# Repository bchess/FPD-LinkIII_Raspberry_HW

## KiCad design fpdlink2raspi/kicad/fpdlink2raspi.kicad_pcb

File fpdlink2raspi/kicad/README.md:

# fpdlink2raspi: KiCad PCB (rebuilt from the Gerbers)

The Altium source (`.PcbDoc`) was never published, so this KiCad 10 project was
**rebuilt** from the fabrication outputs in this repo:

| Input | What it gives |
|-------|---------------|
| `GerberX2/*` (Gerber X2, Altium 20.1) | copper, pads, vias, pours, mask, paste, drills, outline, mechanical layers |
| `Pick Place/*.txt` | reference, side, position and rotation of each part |
| `BOM/*.xlsx` | value, MPN, manufacturer, supplier, Altium LibRef |
| `fpdlink2raspi_SCH_0v4.PDF` | its bookmarks hold Altium's full netlist (net names and pin numbers) |

Open `fpdlink2raspi.kicad_pro` in KiCad 10. `render_top.png` is a KiCad 3D render.

## What you get

* A 4-layer board, 39 x 56 mm, with the stackup from the fab drawing (0.119 / 1.2 / 0.119 mm FR-4, 35 µm Cu, 1.6 mm total).
* 148 footprints: 136 placed parts, the 6 not-fitted parts, 4 mounting holes. Every pad is reconstructed
  exactly: shape, size, corner radius, mask and paste margins, and the segmented exposed-pad paste for U3/U4.
* 100 nets with the schematic's net names. Every pad carries its schematic pin number (U3 pins 1 to 49,
  J1 pins 1 to 15 plus S1/S2, and so on).
* Tracks and arcs, 171 vias (via-in-pad tenting as in Altium), 11 filled zones (inner planes and top pours),
  and the copper text labels ("PoC", "3V3", the zhaw/InES logo, ...).
* A project footprint library, `fpdlink2raspi.pretty`, with all 30 footprints (`fp-lib-table` is included).
* Courtyards (Altium M15/M16) and assembly drawings (M13/M14) inside each footprint. The other Altium
  mechanical layers are kept on named User layers (`User.1` to `User.8`).
* BOM data is in footprint fields. Not-fitted parts (C33, R4, R5, R6, R27, R29) are marked DNP, because the
  variant left them out of pick-and-place. Their identity comes from matching their copper against the netlist.

## How it was checked

* **Gerber round trip.** I exported Gerbers and drills from this KiCad board and compared them geometrically
  with the original Altium files.
  * All 4 copper layers, bottom solder mask and both paste layers match to better than 10 µm.
  * All 185 drill hits match in position and size.
  * The one remaining difference is on top solder mask. KiCad rounds the corners of rectangular pads' mask
    openings with a 50 µm radius; Altium leaves them sharp. That totals 0.16 mm² over the whole board.
* **Netlist.** The pin numbering was solved so that the copper connectivity agrees with the schematic netlist.
  * 21 pins carry a different name in the schematic. All of them are hierarchical-harness aliases of the same
    net: J1's CSI pins to U3's `D_*` nets, U1 GPIOs to U3 GPIOs, I2C through R33/R34, and `REF_CLK`/`TI_*`.
    Each copper net uses the user-given name.
  * There are no shorts between differently named nets and no nets split into islands.
* **KiCad DRC:** 0 clearance errors and 0 unconnected items.
  * There are 48 *courtyard overlap* errors. They are real overlaps in the original Altium layout (Altium
    doesn't check these by default).
  * There are 3 harmless "footprint differs from library" warnings.

## Things that are not in the Gerbers

* **Silkscreen.** The real board has a legend, but no overlay Gerber was published, so `F/B.SilkS` are
  empty. Reference designators are on the Fab layers.
* **Schematic.** There is no `.kicad_sch`. The nets and pin numbers are on the board, so a schematic drawn
  later can be linked with *Update PCB from Schematic*. Use the same references and pin numbers.
* **Altium design rules.** Only the basics are carried over: 0.125 mm clearance, 0.06 mm mask expansion
  (0.05 mm on fine-pitch pads), and 0.15 mm via drills. Altium also had a 1 mm pour-to-diff-pair clearance.
  It is visible in the existing fills, but it's not a KiCad rule.
* **Zones.** The zones are pre-filled with Altium's exact copper. Their outlines follow the filled shapes.
  If you *refill* in KiCad, it recomputes clearances with its own rules, so check the CSI diff pairs and the
  RF lines after a refill.
* **Footprint names.** They are descriptive (for example `VQFN-48-1EP_7x7mm_P0.5mm_EP4.1x4.1mm`). The
  footprints are the Altium ones reconstructed, not KiCad stock library parts, and have no 3D models.
* **BOM values** come from `BOM/*.xlsx`. That includes the 9 V PoC changes described in the top-level
  README, not the values printed in the schematic PDF.

## Regenerating

`conversion/` holds the converter. It runs in KiCad's bundled Python and needs `shapely`, `numpy` and
`pymupdf` installed into a `pylib` directory next to `conversion/`:

```bash
KP=../KiCad.app/Contents/Frameworks/Python.framework/Versions/Current/bin/python3
$KP -m pip install --target pylib "shapely==2.0.6" "numpy<2.1" pymupdf
$KP conversion/build_kicad.py .. out        # writes out/fpdlink2raspi.kicad_pcb etc.
```

`compare.py <fpdlink2raspi dir> <dir with KiCad-exported Gerbers> ''` repeats the Gerber round-trip check.

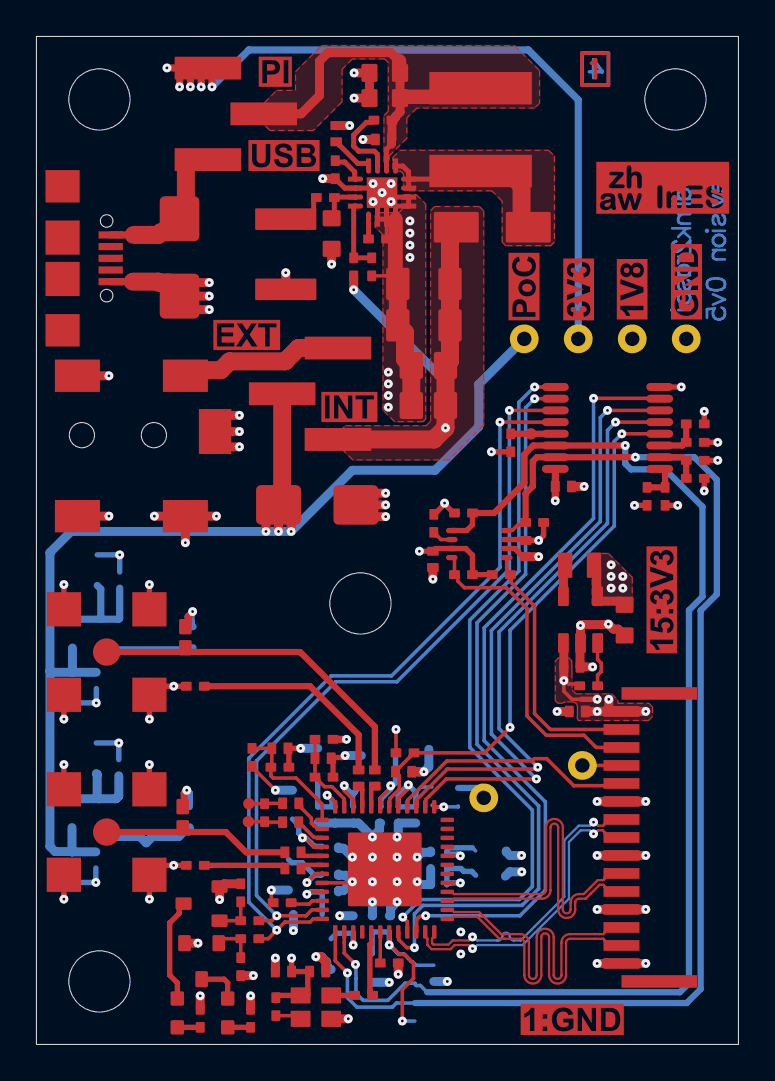
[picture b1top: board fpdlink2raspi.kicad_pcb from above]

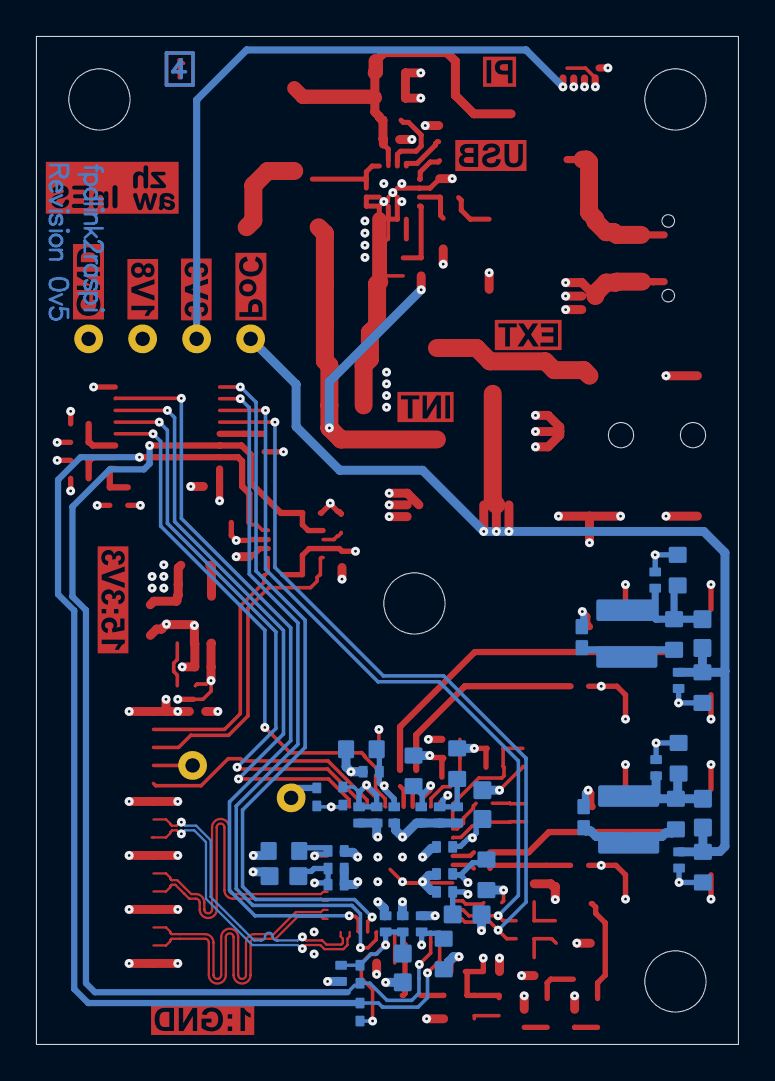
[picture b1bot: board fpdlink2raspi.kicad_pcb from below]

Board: 4 copper layers, 39.0 x 56.0 mm, 148 parts (47 on the bottom side), 84 nets.

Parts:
C1, C3, C4, C5, C6, C8, C10, C12, C14, C20, C24, C30, C37, C38, C42, C53: 100n; C_0402_1005Metric
C2, C21, C22, C25, C26, C28, C31, C32, C35, C40, C44, C46: 10n; C_0402_1005Metric
C7, C9, C11, C13, C23, C29, C51, C52: 10u; C_0603_1608Metric
C15, C17, C36, C41: 33n; C_0402_1005Metric
C16, C18: 15n; C_0402_1005Metric
C19, C27: 1u; C_0402_1005Metric
C33, C57: 4u7; C_0402_1005Metric
C34, C39, C43, C45: 4u7; C_0603_1608Metric
C47, C48: 22u; C_1206_3216Metric
C49, C50: 1u; C_0805_2012Metric
C54: 47n; C_0402_1005Metric
C55: 15n; C_0603_1608Metric
C56: 1u; C_1812_4532Metric
C58: 22u; C_0603_1608Metric
D1: Green, 3.2 V, 140°; LED_0603_1608Metric
D2: Yellow, 2 V, 140°; LED_0603_1608Metric
D3: SMBJ5.0A; D_SMB
D4: B340LA-13-F; D_SMA
D5: SMBJ24A; D_SMB
J1: SFW15R-1ST; Amphenol_SFW15R-1STE1LF_1x15_P1.00mm_Horizontal
J2: PJ-075DH-SMT-TR; CUI_PJ-075CH-SMT_DC_Jack
J3: Micro USB; Wurth_629105136821_USB_Micro-B
L1, L5: 10u; L_Murata_LQH3NP_3.0x3.0mm
L2, L6: 1k 0.4A 0.5R; L_0603_1608Metric
L3, L7: 330R 0.7A 280mR; L_0402_1005Metric
L4, L8: 47R 0.45A 450mR; L_0402_1005Metric
L9, L10, L11, L12: 120R 3A 25mR; L_0603_1608Metric
L13: 12uH, 2.6A; L_Wurth_WE-LQS-6045
L14: 2u2; L_Murata_DFE201612E
MH1, MH2, MH3, MH4: MountingHole; MountingHole_3.4mm_NPTH
Q1, Q2: BSS138-13-F; SOT-23
R1, R18, R19, R26, R35, R36, R37, R41, R43: 0R; R_0402_1005Metric
R2, R3, R29, R32, R42: 10k; R_0402_1005Metric
R4, R5, R6, R7, R8, R9, R14: 1k; R_0402_1005Metric
R10, R11, R25, R27: 4k7; R_0402_1005Metric
R12, R13, R33, R34: 47k; R_0402_1005Metric
R15: 1k2; R_0402_1005Metric
R16, R39: 390R; R_0402_1005Metric
R17, R22: 4k02; R_0603_1608Metric
R20, R21: 118k; R_0402_1005Metric
R23, R24: 49R9; R_0402_1005Metric
R28: 78k7; R_0402_1005Metric
R30: 100R; R_0402_1005Metric
R31: 97k6; R_0402_1005Metric
R38: 63k4; R_0402_1005Metric
R40: 60k4; R_0402_1005Metric
TP1: 0v1 27.04.20 gana Review release.; TestPoint_THTPad_D1.6mm_Drill0.8mm
TP2: PIC301; TestPoint_Pad_D0.635mm
TP3: A0; TestPoint_THTPad_D1.6mm_Drill0.8mm
TP4, TP5: TestPoint; TestPoint_Pad_D0.635mm
TP6, TP7, TP9: TestPoint; TestPoint_THTPad_D1.6mm_Drill0.8mm
TP8: 2 MHz (1.6 - 2.6 MHz); TestPoint_THTPad_D1.6mm_Drill0.8mm
U1: TCA9534APW; TSSOP-16_4.4x5mm_P0.65mm
U2: TCA9406DCUR; TI_US8_DCU_2.3x2.0mm_P0.5mm
U3: DS90UB954TRGZxQ1; VQFN-48-1EP_7x7mm_P0.5mm_EP4.1x4.1mm
U4: TPS55340RTE; WQFN-16-1EP_3x3mm_P0.5mm_EP1.7x1.7mm
U5: LM3671MFX-1.8/NOPB; SOT-23-5
X1, X2: SMA JACK STR; Molex_73251-1350_SMA_Vertical
X3, X4: 1241150-3; TE_1241150-3_1x03_P2.54mm_SMD
Y1: SG-210STF 25.0000M; Oscillator_Epson_SG-210STF_2.5x2.0mm

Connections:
1V8: C1.2, C2.2, C3.2, C6.2, C58.2, L9.1, L10.1, L11.1, L12.1, L14.2, R2.1, R3.2, R4.2, R5.2, R6.2, R10.2, R11.2, R14.1, R27.2, R28.2, R29.2, TP9.1, U1.16, U2.3, U5.4, Y1.4
3V3: C4.2, C5.2, C57.2, J1.15, R12.2, R13.2, R15.2, R16.2, R43.1, TP6.1, U2.7, U5.1, X3.3
D_CLK_0_N: J1.8, U3.11
D_CLK_0_P: J1.9, U3.12
D_DATA_0_N: J1.2, U3.13
D_DATA_0_P: J1.3, U3.14
D_DATA_1_N: J1.5, U3.15
D_DATA_1_P: J1.6, U3.16
GND: C1.1, C2.1, C3.1, C4.1, C5.1, C6.1, C7.1, C8.1, C9.1, C10.1, C11.1, C12.1, C13.1, C14.1, C19.1, C20.1, C21.1, C22.1, C23.1, C24.1, C25.1, C26.1, C27.1, C28.1, C29.1, C30.1, C31.1, C32.1, C33.1, C34.1, C35.1, C37.1, C38.1, C39.1, C40.1, C42.1, C43.1, C44.1, C45.1, C46.1, C47.2, C48.2, C49.2, C50.1, C51.1, C52.1, C53.1, C54.1, C55.1, C56.1, C57.1, C58.1, D3.2, D5.2, J1.1, J1.4, J1.7, J1.10, J2.2, J2.3, J2.4, J2.5, J3.5, Q1.2, Q2.2, R7.1, R8.1, R9.1, R20.1, R21.1, R23.1, R24.1, R31.1, R32.1, R35.1, R36.1, R40.1, R41.1, R42.1, TP8.1, U1.8, U2.2, U3.44, U3.49, U4.6, U4.10, U4.11, U4.12, U4.13, U4.14, U4.17, U5.2, X1.2, X1.3, X1.4, X1.5, X2.2, X2.3, X2.4, X2.5, Y1.2
IDX: C38.2, R29.1, R32.2, U3.35
MODE: C37.2, R28.1, R31.2, U3.37
NetC9_2: C9.2, C10.2, L1.1, L2.2, R17.1
NetC13_2: C13.2, C14.2, L5.1, L6.2, R22.1
NetC15_1: C15.1, U3.41
NetC15_2: C15.2, L4.2, X1.1
NetC16_1: C16.1, R23.2
NetC16_2: C16.2, U3.42
NetC17_1: C17.1, U3.32
NetC17_2: C17.2, L8.2, X2.1
NetC18_1: C18.1, R24.2
NetC18_2: C18.2, U3.33
NetC23_2: C23.2, C24.2, C25.2, C26.2, L10.2, U3.36, U3.45
NetC27_2: C27.2, C28.2, L11.2, U3.17
NetC29_2: C29.2, C30.2, C31.2, C32.2, L12.2, U3.31, U3.40
NetC33_2: C33.2, R27.1, U1.4, U3.30
NetC34_2: C34.2, C35.2, U3.3
NetC36_1: C36.1, R30.2, TP4.1
NetC36_2: C36.2, U3.38
NetC39_2: C39.2, C40.2, U3.20
NetC41_1: C41.1, R30.1, TP5.1
NetC41_2: C41.2, U3.39
NetC43_2: C43.2, C44.2, U3.43
NetC45_2: C45.2, C46.2, U3.34
NetC47_1: C47.1, C48.1, C49.1, C50.2, D4.1, R38.2, X4.3
NetC51_2: C51.2, C52.2, C53.2, L13.1, R37.1, U4.2, X3.2
NetC54_2: C54.2, U4.4
NetC55_2: C55.2, R39.1, U4.7
NetC56_2: C56.2, R39.2
NetD1_1: D1.1, Q1.3
NetD1_2: D1.2, R15.1
NetD2_1: D2.1, Q2.3
NetD2_2: D2.2, R16.1
NetD3_1: D3.1, J3.1, X3.1
NetD4_2: D4.2, L13.2, U4.1, U4.15, U4.16
NetJ1_11: J1.11, U3.28
NetJ1_12: J1.12, TP3.1
NetJ1_13: J1.13, R12.1, U2.8
NetJ1_14: J1.14, R13.1, U2.1
NetJ2_1: J2.1, X4.1
NetL1_2: L1.2, L3.1, R17.2
NetL3_2: L3.2, L4.1
NetL5_2: L5.2, L7.1, R22.2
NetL7_2: L7.2, L8.1
NetL14_1: L14.1, U5.5
NetQ1_1: Q1.1, R18.2, R20.2
NetQ2_1: Q2.1, R19.2, R21.2
NetR1_1: R1.1, Y1.3
NetR2_2: R2.2, Y1.1
NetR3_1: R3.1, TP2.1, U1.13
NetR4_1: R4.1, R7.2, U1.1
NetR5_1: R5.1, R8.2, U1.2
NetR6_1: R6.1, R9.2, U1.3
NetR10_1: R10.1, R33.1, U1.15, U2.4, U3.1
NetR11_1: R11.1, R34.1, U1.14, U2.5, U3.2
NetR14_2: R14.2, U2.6
NetR25_1: R25.1, R26.2, U3.25
NetR35_2: R35.2, U3.6
NetR36_2: R36.2, U3.46
NetR37_2: R37.2, U4.3
NetR38_1: R38.1, R42.2, U4.8
NetR40_2: R40.2, U4.9
NetR41_2: R41.2, U4.5
NetR43_2: R43.2, U5.3
NetTP1_1: R26.1, TP1.1
NetU1_5: U1.5, U3.27
NetU1_6: U1.6, U3.26
NetU1_7: U1.7, U3.10
NetU1_9: U1.9, U3.9
NetU3_8: U1.10, U3.8
REF_CLK: R1.2, U3.5
TI_LOCK: R19.1, U1.12, U3.48
TI_PASS: R18.1, U1.11, U3.47
VDDIO: C19.2, C20.2, C21.2, C22.2, C42.2, L9.2, R25.2, R33.2, R34.2, U3.7, U3.29
V_POC: C7.2, C8.2, C11.2, C12.2, D5.1, L2.1, L6.1, TP7.1, X4.2

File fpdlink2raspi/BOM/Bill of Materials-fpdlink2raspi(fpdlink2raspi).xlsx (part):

Name | Description | Designator | Quantity | LibRef | Supplier 1 | Supplier Part Number 1 | Manufacturer 1 | Manufacturer Part Number 1
100n | SMD 100 nF, 50V, X7R, 0402, 10% | C1, C3, C4, C5, C6, C8, C10, C12, C14, C20, C24, C30, C37, C38, C42, C53 | 16 | C0402_100N_X7R_50V_10PCT | Mouser | 81-GCM155R71H104KE2J | Murata | GCM155R71H104KE02J
10n | SMD 10 nF, 16V, X7R, 0402, 10% | C2 | 1 | C0402_010N_X7R_16V_10PCT | Mouser | 81-GRM36X103K16 | Murata | GRM155R71C103KA01D
10u | 10µF, 25V, +/-20%, X5R, 0603 | C7, C9, C11, C13, C23, C29, C51, C52 | 8 | C0603_010U_X5R_25V | Digi-Key | 490-7202-6-ND | Murata | GRM188R61E106MA73D
33n | SMD 33 nF, 50V, X7R, 0402, 10% | C15, C17, C36, C41 | 4 | C0402_033N_X7R_50V_10PCT | Digi-Key | 445-6896-1-ND | TDK | CGA2B3X7R1H333K050BB
15n | SMD 15 nF, 50V, X7R, 0402, 10% | C16, C18 | 2 | C0402_015N_X7R_50V_10PCT | Digi-Key | 445-6894-1-ND | TDK | CGA2B3X7R1H153K050BB
1u | SMD 1 µF, 35V, X5R, 0402, 10% | C19, C27 | 2 | C0402_001U_X5R_35V_10PCT | Digi-Key | 587-6008-1-ND | Taiyo Yuden | GMK105ABJ105KV-F
10n | SMD 10 nF, 50V, X7R, 0402, 10% | C21, C22, C25, C26, C28, C31, C32, C35, C40, C44, C46 | 11 | C0402_010N_X7R_50V_10PCT | Digi-Key | 490-4762-1-ND | Murata | GCM155R71H103KA55D
4u7 | 4.7µF, 25V, +/-10%, X5R, 0603 | C34, C39, C43, C45 | 4 | C0603_04U7_X5R_25V | Digi-Key | 490-7203-1-ND | Murata | GRM188R61E475KE11D
22u | 22µF ±20% 35V Ceramic Capacitor X5R 1206 (3216 Metric) | C47, C48 | 2 | C1206_022U_X5R_35V_20PCT | Digi-Key | 445-8045-1-ND | TDK | C3216X5R1V226M160AC
1u | 1µF ±10% 35V Ceramic Capacitor X7R 0805 (2012 Metric) | C49, C50 | 2 | C0805_001U_X7R_35V_10PCT | Digi-Key | 587-1438-1-ND | Taiyo Yuden | GMK212B7105KG-T
47n | 0.047µF ±10% 16V Ceramic Capacitor X7R 0402 (1005 Metric) | C54 | 1 | C0402_047N_X7R_16V_10PCT | Mouser | 81-GRM155R71C473KA01 | Murata | GRM155R71C473KA01D
15n | 15000pF ±5% 25V Ceramic Capacitor C0G, NP0 0603 (1608 Metric) | C55 | 1 | C0603_15N_C0G_25V_5PCT |  |  | KEMET | C0603C153J3GACTU
1u | 1µF ±10% 50V Ceramic Capacitor X7R 1812 (4532 Metric) | C56 | 1 | C1812_001U_X7R_50V_10PCT | LCSC | C452759 | KEMET | C1812C105K5RACTU
4u7 | SMD 4.7 µF, 10V, X5R, 0402, 20% | C57 | 1 | C0402_04U7_X5R_10V_20PCT | Mouser | 81-GRM155R61A475MEAD | Murata | GRM155R61A475MEAAD
22u | SMD 22 µF, 6.3V, X5R, 0603, 20% | C58 | 1 | C0603_022U_X5R_6V3_20PCT | Digi-Key | 490-13241-1-ND | Murata | GRM186R60J226ME15D
Green, 3.2 V, 140° | WL-SMCD SMD Mono-color Chip LED Diffused, size 0603, Green, 3.2 V, 140° | D1 | 1 | D_WE_150060GS55040 | Mouser | 710-150060GS55040 | Wurth Electronics | 150060GS55040
Yellow, 2 V, 140° | WL-SMCD SMD Mono-color Chip LED Diffused, size 0603, Yellow, 2 V, 140° | D2 | 1 | D_WE_150060YS55040 | Mouser | 710-150060YS55040 | Wurth Electronics | 150060YS55040
SMBJ5.0A | 9.2V Clamp 65.2A Ipp Tvs Diode Surface Mount DO-214AA (SMBJ) | D3 | 1 | D_TVS_5V0_Power | Digi-Key | SMBJ5.0A-E3/52GICT-ND | Vishay Semiconductors | SMBJ5.0A-E3/52
B340LA-13-F | Diode Schottky 40V 3A Surface Mount SMA | D4 | 1 | D_DIODES_B340LA-13-F | Digi-Key | B340LA-FDICT-ND | Diodes | B340LA-13-F
SMBJ24A | 38.9V Clamp 15.5A Ipp Tvs Diode Surface Mount DO-214AA (SMBJ) | D5 | 1 | D_TVS_24V | Digi-Key | SMBJ24ALFCT-ND | Littelfuse | SMBJ24A
SFW15R-1ST | 15 Position FFC, FPC Connector Contacts, Bottom 0.039" (1.00mm) Surface Mount, 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 | J1 | 1 | J_PI_CAMV2_BOTTOM | Mouser | 649-SFW15R-1STE1LF | Amphenol ICC | SFW15R-1STE1LF
PJ-075DH-SMT-TR | 1.3 x 3.7 mm, 3.5 A, Horizontal, Surface Mount _SMT_, Shielded, Dc Power Jack C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 | J2 | 1 | J_CUI_PJ-075CH-SMT-TR | Mouser | 490-PJ-075DH-SMT-TR | Same Sky (formerly CUI Devices) | PJ-075DH-SMT-TR
Micro USB | WR-COM Micro USB SMT Type B | J3 | 1 | J_WE_629105136821 | Digi-Key | 732-3155-1-ND | Wurth Electronics | 629105136821
10u | LQH3NPZ100MJR SMD Shielded coil, 10 µH, 0.81 A, 0.24 Ω, 30 MHz | L1, L5 | 2 | L1212_SHCOIL_10U_0A81_0R24_20PCT | Arrow | LQH3NPZ100MJRL | Murata | LQH3NPZ100MJRL
1k 0.4A 0.5R | BLM18AG102SN1D SMD Ferrite Bead 1kΩ@100MHz, 25%, 0.4A, DC 500mΩ | L2, L6 | 2 | L0603_BEAD_001K_0A4_25PCT | Mouser | 81-BLM11A102S | Murata | BLM18AG102SN1D
330R 0.7A 280mR | MPZ1005S331ETD25 SMD Ferrite Bead 330Ω@100MHz ±25%, 700 mA, DC 280 mΩ | L3, L7 | 2 | L0402_BEAD_330R_0A7_25PCT | Mouser | 810-MPZ1005S331ETD25 | TDK | MPZ1005S331ETD25
47R 0.45A 450mR | MPZ1005F470ETD25 SMD Ferrite Bead 47Ω@100MHz ±25%, 450 mA, DC 450 mΩ | L4, L8 | 2 | L0402_BEAD_047R_0A45_25PCT | Mouser | 810-MPZ1005F470ETD25 | TDK | MPZ1005F470ETD25
120R 3A 25mR | BLM18SG121TN1D SMD Ferrite Bead 120Ω@100MHz, 25%, 3A, DC 25mΩ | L9, L10, L11, L12 | 4 | L0603_BEAD_120R_3A_25PCT | Mouser | 81-BLM18SG121TN1D | Murata | BLM18SG121TN1D
12uH, 2.6A | WE-LQS SMT Power Inductor, size 6045, 12uH, 2.6A | L13 | 1 | L_WE_74404064120 | Digi-Key | 732-5551-1-ND | Wurth Electronics | 74404064120
2u2 | DFE201210U-2R2M=P2 SMD Shielded coil, 2.2 µH ±20%, 1.2 A, 0.228 Ω | L14 | 1 | L0805_SHCOIL_2U2_1A2_R228_20PCT | Mouser | 81-DFE201612E-2R2MP2 | Murata | DFE201612E-2R2M=P2
QPC02SXGN-RC | 2 (1 x 2) Position Shunt Connector Black Open Top 0.100" (2.54mm) Gold | M1, M2 | 2 | M_JUMPER_2.54 | Digi-Key | S9337-ND | Sullins | QPC02SXGN-RC
BSS138-13-F | N-Channel Digital FET 50V, 0.2A, 3.5Ω | Q1, Q2 | 2 | Q_DIODES_BSS138-13-F | Mouser | 621-BSS138-13-F | Diodes | BSS138-13-F
0R | SMD 0 Ω, 0402, 1.5 A, 20 mΩ Rmax | R1, R18, R19, R26, R35, R36, R37, R41, R43 | 9 | R0402_000R_1A5_0R02 | Mouser | 71-CRCW0402-0-E3 | Vishay | CRCW04020000Z0ED
10k | SMD 10 kΩ, 1%, 50V, 0402, 1/16W, ±100ppm | R2, R3, R32, R42 | 4 | R0402_010K_50V_0W063_100PPM | Mouser | 71-CRCW0402-10K-E3 | Vishay | CRCW040210K0FKED
1k | SMD 1 kΩ, 0.1%, 50V, 0402, 1/16W, ±25ppm | R7, R8, R9 | 3 | R0402_001K_50V_0W063_25PPM_0PCT1 | Digi-Key | P1.0KDCCT-ND | Panasonic | ERA-2AEB102X
4k7 | SMD 4.7 kΩ, 1%, 50V, 0402, 1/16W, ±100ppm | R10, R11, R25 | 3 | R0402_04K7_50V_0W063_100PPM | Digi-Key | 541-4.70KLCT-ND | Vishay | CRCW04024K70FKED
47k | SMD 47 kΩ, 1%, 50V, 0402, 1/16W, ±100ppm | R12, R13, R33, R34 | 4 | R0402_047K_50V_0W063_100PPM | Mouser | 71-CRCW0402-47K-E3 | Vishay | CRCW040247K0FKED
1k | SMD 1 kΩ, 0.1%, 50V, 0402, 1/16W, ±25ppm | R14 | 1 | R0402_001K_50V_0W063_100PPM | Digi-Key | 541-1.00KLDKR-ND | Vishay Dale | CRCW04021K00FKED
1k2 | SMD 1.2 kΩ, 1%, 50V, 0402, 1/16W, ±100ppm | R15 | 1 | R0402_01K2_50V_0W063_100PPM | Digi-Key | 541-1.20KLCT-ND | Vishay | CRCW04021K20FKED
390R | SMD 390 Ω, 1%, 50V, 0402, 1/16W, ±100ppm | R16 | 1 | R0402_390R_50V_0W063_100PPM | Digi-Key | 541-390LCT-ND | Vishay | CRCW0402390RFKED
4k02 | SMD 4.02 kΩ, 1%, 75V, 0603, 1/10W, ±100ppm | R17, R22 | 2 | R0603_4K02_75V_0W100_100PPM | Digi-Key | 541-4.02KHCT-ND | Vishay | CRCW06034K02FKEA
118k | SMD 118 kΩ, 1%, 50V, 0402, 1/16W, ±100ppm | R20, R21 | 2 | R0402_118K_50V_0W063_100PPM | Digi-Key | 541-118KLCT-ND | Vishay | CRCW0402118KFKED
49R9 | SMD 49.9 Ω, 1%, 50V, 0402, 1/16W, ±100ppm | R23, R24 | 2 | R0402_49R9_50V_0W063_100PPM | Mouser | 71-CRCW0402-49.9-E3 | Vishay | CRCW040249R9FKED
78k7 | SMD 78.7 kΩ, 1%, 50V, 0402, 1/16W, ±100ppm | R28 | 1 | R0402_78K7_50V_0W063_100PPM | Digi-Key | 541-78.7KLCT-ND | Vishay | CRCW040278K7FKED
100R | SMD 100 Ω, 1%, 50V, 0402, 1/16W, ±100ppm | R30 | 1 | R0402_100R_50V_0W063_100PPM | Digi-Key | 541-100LCT-ND | Vishay Dale | CRCW0402100RFKED
97k6 | SMD 97.6 kΩ, 1%, 50V, 0402, 1/16W, ±100ppm | R31 | 1 | R0402_97K6_50V_0W063_100PPM | Mouser | 71-CRCW0402-97.6K-E3 | Vishay | CRCW040297K6FKED
63k4 | SMD 63.4 kΩ, 1%, 50V, 0402, 1/16W, ±100ppm | R38 | 1 | R0402_63K4_50V_0W063_100PPM | Mouser | 71-CRCW0402-63.4K-E3 | Vishay | CRCW040263K4FKED
390R | SMD 390 Ω, 1%, 50V, 0402, 1/16W, ±100ppm | R39 | 1 | R0402_390R_50V_0W063_100PPM | Digi-Key | 541-390LCT-ND | Vishay | CRCW0402390RFKED
60k4 | 60.4 kOhms ±1% 0.063W, 1/16W Chip Resistor 0402 (1005 Metric) Automotive AEC-Q2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 | R40 | 1 | R0402_60K4_50V_0W063_100PPM | Digi-Key | 541-60.4KLCT-ND | Vishay | CRCW040260K4FKED
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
